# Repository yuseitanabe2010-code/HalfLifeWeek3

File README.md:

This is a MIDI keyboard, but much more advanced than the beginner's one. I made it because I'm pretty interested in making music (though I'm not very god at it) and I though it would be the perfect project to make that happen.

It features a full 12 note octave, and also the keys are mechnical keyboards. Also, you have the ability to switch between drums and keyboard with the flick of a switch. There are two buttons that let you lower or raise the octave. Finally, there is a voulme slider. There is art on the top left corner of Nujabes and his album Luv Sic Hexalogy because I love both of them a lot, RIP.

This is what it looks like, and as you can see all of the parts are on the top right, art on top left, and keys down at the bottom. I think it looks pretty cool.

This is what it will look like when it's done, just with actual keycaps on there. So don't worry, it will look a lot nicer.

This is the bill of materials.

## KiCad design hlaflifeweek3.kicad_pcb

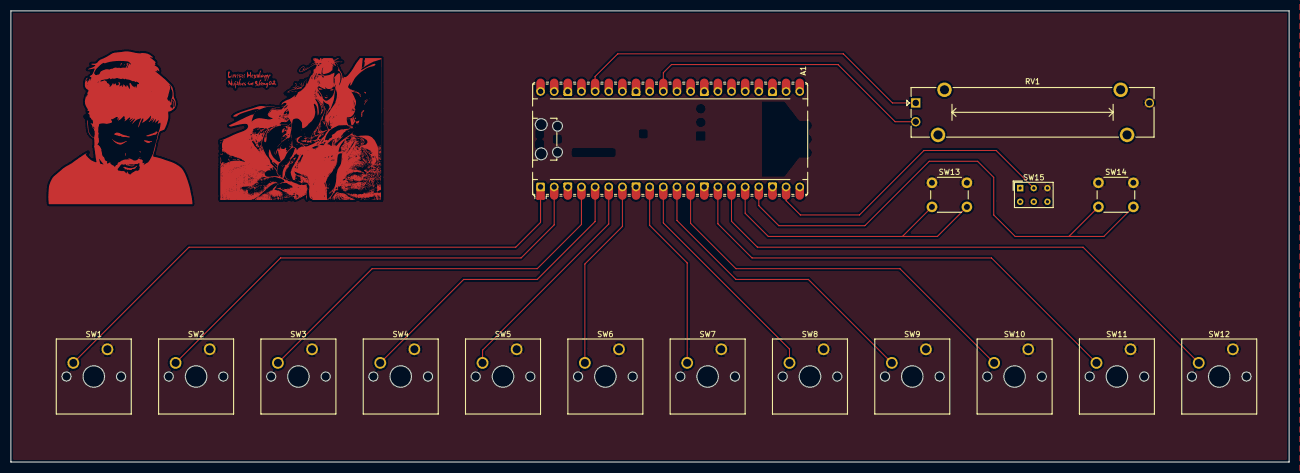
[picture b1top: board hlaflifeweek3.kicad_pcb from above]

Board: 2 copper layers, 238.0 x 84.0 mm, 19 parts (0 on the bottom side), 18 nets.

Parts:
A1: RaspberryPi_Pico; RaspberryPi_Pico_Common_Unspecified
G: LOGO; luvsic
RV1: R_Potentiometer; Potentiometer_Bourns_PTA3043_Single_Slide
SW1, SW2, SW3, SW4, SW5, SW6, SW7, SW8, SW9, SW10, SW11, SW12: SW_Push; SW_Cherry_MX_1.00u_PCB
SW13, SW14: SW_Push; SW_PUSH_6mm
SW15: SW_SPDT; SW_NKK_GW12LJP
g: LOGO; nujabes

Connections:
GND: RV1.3, SW1.1, SW2.1, SW3.1, SW4.1, SW5.1, SW6.1, SW7.1, SW8.1, SW9.1, SW10.1, SW11.1, SW12.1, SW13.1, SW14.1, SW15.3 (C)
unnamed: A1.36 (3V3), RV1.1
unnamed: A1.1 (GPIO0), SW1.2
unnamed: A1.2 (GPIO1), SW2.2
unnamed: A1.4 (GPIO2), SW3.2
unnamed: A1.5 (GPIO3), SW4.2
unnamed: A1.6 (GPIO4), SW5.2
unnamed: A1.7 (GPIO5), SW6.2
unnamed: A1.9 (GPIO6), SW7.2
unnamed: A1.10 (GPIO7), SW8.2
unnamed: A1.11 (GPIO8), SW9.2
unnamed: A1.12 (GPIO9), SW10.2
unnamed: A1.14 (GPIO10), SW11.2
unnamed: A1.15 (GPIO11), SW12.2
unnamed: A1.16 (GPIO12), SW13.2
unnamed: A1.17 (GPIO13), SW14.2
unnamed: A1.19 (GPIO14), SW15.2 (B)
unnamed: A1.31 (GPIO26_ADC0), RV1.2
